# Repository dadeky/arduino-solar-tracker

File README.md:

# arduino-solar-tracker
Solar tracker solution

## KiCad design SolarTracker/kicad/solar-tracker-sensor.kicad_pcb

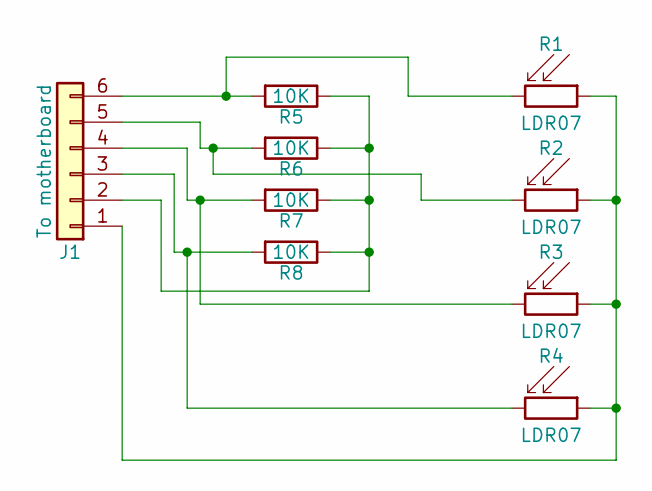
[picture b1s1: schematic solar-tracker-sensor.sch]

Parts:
J1: To motherboard; Wafer_Vertical17.5x5.8x7RM2.5-6
R1, R2, R3, R4: LDR07; Resistor_LDR_5.1x4.3_RM3.4
R5, R6, R7, R8: 10K; Resistor_Vertical_RM5mm

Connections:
unnamed: J1.1, R1.1, R2.1, R3.1, R4.1
unnamed: J1.2, R5.1, R6.1, R7.1, R8.1
unnamed: J1.3, R4.2, R8.2
unnamed: J1.4, R3.2, R7.2
unnamed: J1.5, R2.2, R6.2
unnamed: J1.6, R1.2, R5.2

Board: 2 copper layers, 9 parts (0 on the bottom side), 6 nets, no tracks yet.

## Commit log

2018-01-13 Initial
2018-01-15 kicad and stuff
2018-01-16 Getting there
2018-02-02 Devel
2018-06-04 kicad
2018-06-19 Small updates.
2018-06-22 Some
2018-06-22 Built
2018-07-12 Photon
